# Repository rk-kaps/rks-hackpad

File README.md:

<h1 align="center">12-Key RP2040 Hackpad</h1>

<p align="center">
  A custom 12-key macropad built around the Seeed XIAO RP2040, featuring per-key RGB, an OLED display, and a 3D printed case.
</p>

<hr>

<h2>Motivation</h2>
<ul>

This Hackpad began as a simple volume controller. It evolved into a fully-featured macropad focused on:

- Speeding up workflows
- Reducing repetitive actions
- Providing intuitive visual feedback
- Maximizing functionality within hardware constraints

</ul>

<h2>Project Highlights</h2>
<ul>

- Dual-core RP2040 at up to 133MHz via the compact Seeed XIAO form factor
- Per-key RGB lighting using SK6812 MINI-E reverse-mount LEDs for clean underglow
- 0.91" OLED display for real-time visual feedback and animations
- Keyboard matrix protected by 1N4148 diodes for reliable n-key rollover
- Brass heatset inserts for durable, reusable screw connections in the 3D printed case
- Compact 12-key layout in a custom 3D printed two-piece shell

</ul>

<h2>Firmware Features</h2>
<ul>

- Acts as a USB numpad  
- LED pulses under each key when pressed  
- OLED plays a cat GIF on loop  

</ul>

<hr>

<h2>PCB & Schematic</h2>

<p align="center">
  
  <br><em>Schematic</em>
</p>

<p align="center">
  
  <br><em>PCB Layout (KiCad)</em>
</p>

<p align="center">
  
  <br><em>PCB 3D Render</em>
</p>

<hr>

<h2>Case Design</h2>

<p align="center">
  
  <br><em>Case CAD</em>
</p>

<hr>

<h2>Bill of Materials</h2>

> A full BOM with pricing and purchase links is available as a separate file.

| Part | Quantity |
|------|----------|
| Seeed XIAO RP2040 | 1 |
| MX-Style Switches | 12 |
| Through-hole 1N4148 Diodes | 12 |
| SK6812 MINI-E LEDs | 12 |
| 0.91" OLED Display (SSD1306 I2C 128×32) | 1 |
| Blank DSA Keycaps | 12 |
| M3×16 mm Cap Head Screws | 4 |
| M3×5 mm Brass Heatset Inserts | 4 |
| 3D Printed Case Top | 1 |
| 3D Printed Case Bottom | 1 |

<hr>

<h2>Firmware</h2>

Firmware is located in the `Deploy` folder. Flash directly to the RP2040 via USB drag-and-drop.

<hr>

<h2>Acknowledgements</h2>
<ul>

- Good people of Hack Club  

</ul>

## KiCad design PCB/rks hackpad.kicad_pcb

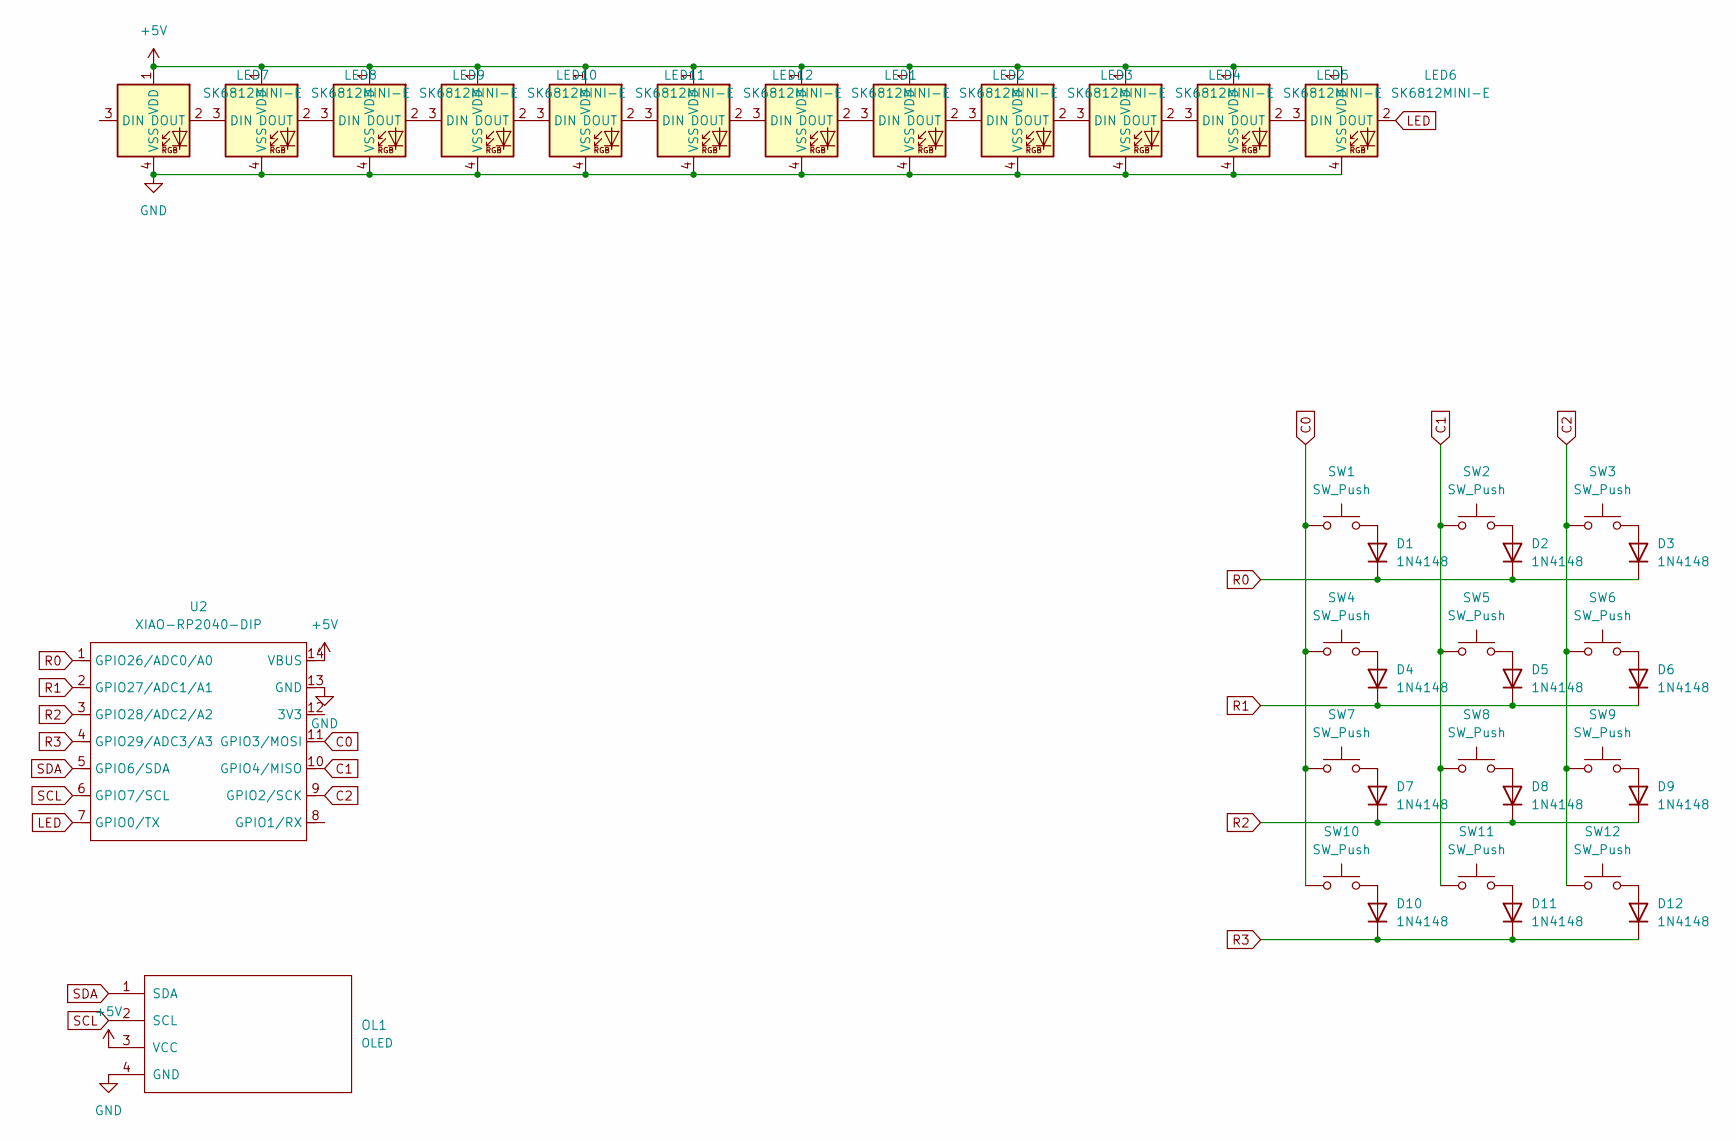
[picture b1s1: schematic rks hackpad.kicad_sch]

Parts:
D1, D2, D3, D4, D5, D6, D7, D8, D9, D10, D11, D12: 1N4148; D_DO-35_SOD27_P7.62mm_Horizontal
LED1, LED2, LED3, LED4, LED5, LED6, LED7, LED8, LED9, LED10, LED11, LED12: SK6812MINI-E; LED_6028R
OL1: OLED; Adafruit_SSD1306
SW1, SW2, SW3, SW4, SW5, SW6, SW7, SW8, SW9, SW10, SW11, SW12: SW_Push; SW_Cherry_MX_1.00u_PCB
U2: XIAO-RP2040-DIP

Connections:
+5V: LED1.1 (VDD), LED2.1 (VDD), LED3.1 (VDD), LED4.1 (VDD), LED5.1 (VDD), LED6.1 (VDD), LED7.1 (VDD), LED8.1 (VDD), LED9.1 (VDD), LED10.1 (VDD), LED11.1 (VDD), LED12.1 (VDD), OL1.3 (VCC), U2.14 (VBUS)
C0: SW1.1, SW4.1, SW7.1, SW10.1, U2.11 (GPIO3/MOSI)
C1: SW2.1, SW5.1, SW8.1, SW11.1, U2.10 (GPIO4/MISO)
C2: SW3.1, SW6.1, SW9.1, SW12.1, U2.9 (GPIO2/SCK)
GND: LED1.4 (VSS), LED2.4 (VSS), LED3.4 (VSS), LED4.4 (VSS), LED5.4 (VSS), LED6.4 (VSS), LED7.4 (VSS), LED8.4 (VSS), LED9.4 (VSS), LED10.4 (VSS), LED11.4 (VSS), LED12.4 (VSS), OL1.4 (GND), U2.13 (GND)
LED: LED6.2 (DOUT), U2.7 (GPIO0/TX)
unnamed: D1.2 (A), SW1.2
unnamed: D2.2 (A), SW2.2
unnamed: D3.2 (A), SW3.2
unnamed: D4.2 (A), SW4.2
unnamed: D5.2 (A), SW5.2
unnamed: D6.2 (A), SW6.2
unnamed: D7.2 (A), SW7.2
unnamed: D8.2 (A), SW8.2
unnamed: D9.2 (A), SW9.2
unnamed: D10.2 (A), SW10.2
unnamed: D11.2 (A), SW11.2
unnamed: D12.2 (A), SW12.2
unnamed: LED1.3 (DIN), LED12.2 (DOUT)
unnamed: LED1.2 (DOUT), LED2.3 (DIN)
unnamed: LED2.2 (DOUT), LED3.3 (DIN)
unnamed: LED3.2 (DOUT), LED4.3 (DIN)
unnamed: LED4.2 (DOUT), LED5.3 (DIN)
unnamed: LED5.2 (DOUT), LED6.3 (DIN)
unnamed: LED7.2 (DOUT), LED8.3 (DIN)
unnamed: LED8.2 (DOUT), LED9.3 (DIN)
unnamed: LED9.2 (DOUT), LED10.3 (DIN)
unnamed: LED10.2 (DOUT), LED11.3 (DIN)
unnamed: LED11.2 (DOUT), LED12.3 (DIN)
R0: D1.1 (K), D2.1 (K), D3.1 (K), U2.1 (GPIO26/ADC0/A0)
R1: D4.1 (K), D5.1 (K), D6.1 (K), U2.2 (GPIO27/ADC1/A1)
R2: D7.1 (K), D8.1 (K), D9.1 (K), U2.3 (GPIO28/ADC2/A2)
R3: D10.1 (K), D11.1 (K), D12.1 (K), U2.4 (GPIO29/ADC3/A3)
SCL: OL1.2 (SCL), U2.6 (GPIO7/SCL)
SDA: OL1.1 (SDA), U2.5 (GPIO6/SDA)

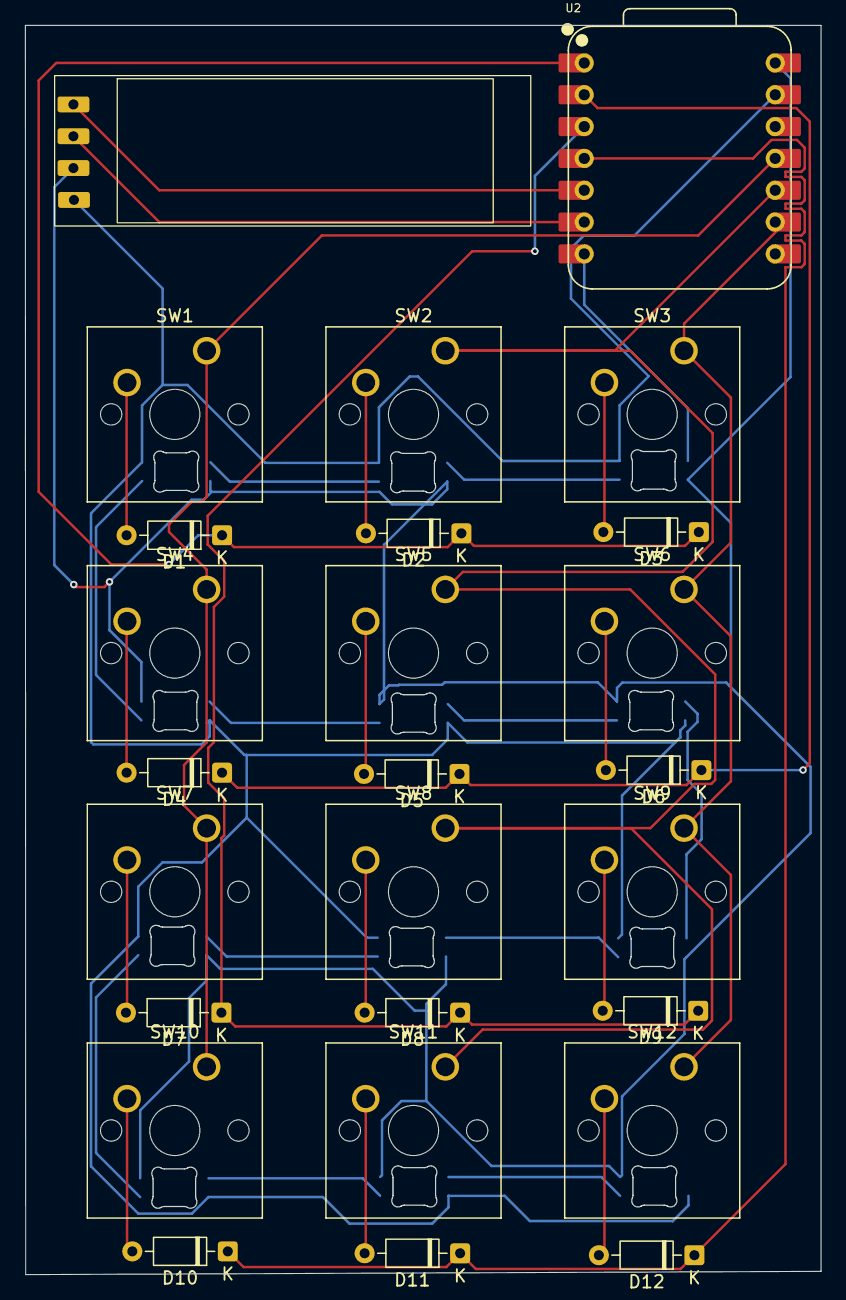
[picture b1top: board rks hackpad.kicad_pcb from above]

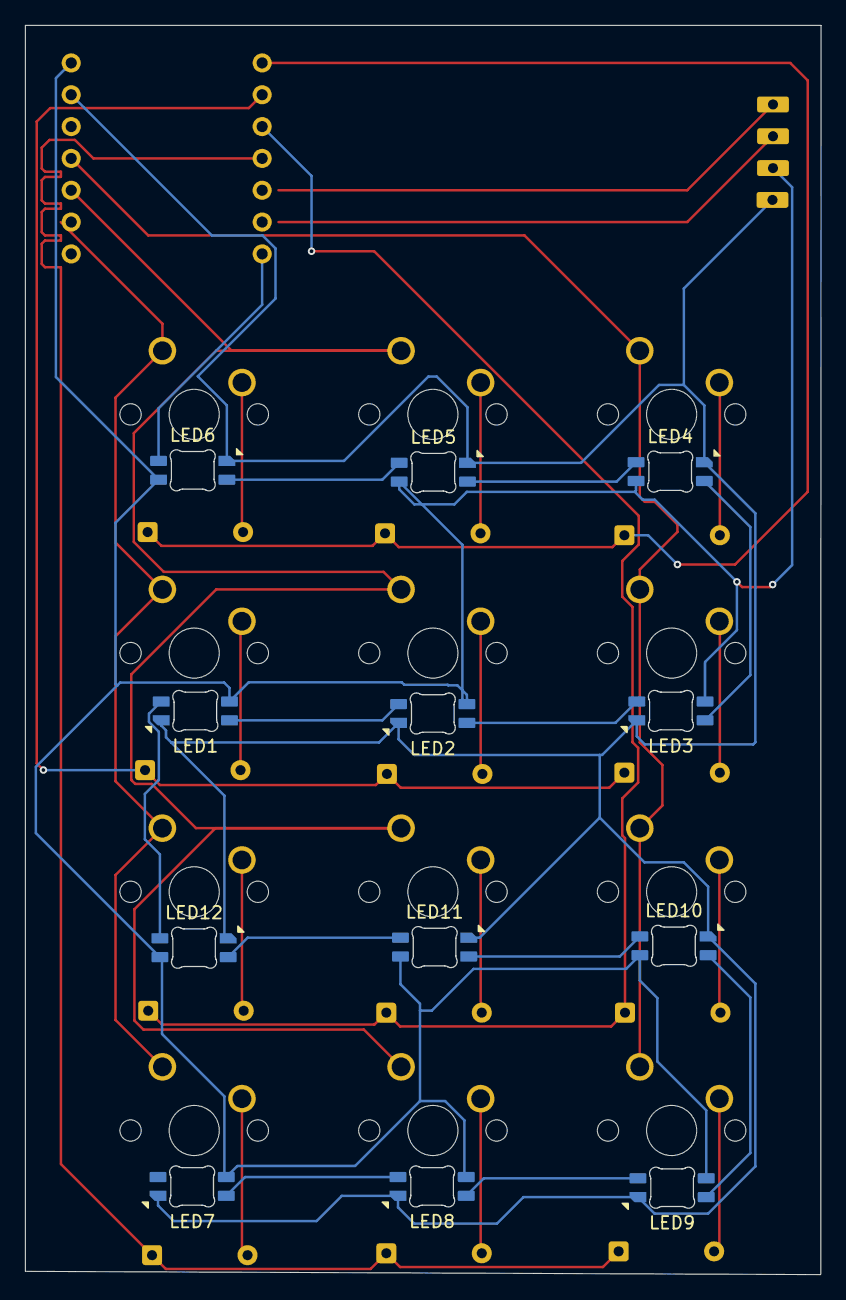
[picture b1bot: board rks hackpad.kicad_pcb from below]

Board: 2 copper layers, 63.5 x 99.7 mm, 38 parts (12 on the bottom side), 35 nets.

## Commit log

2026-04-04 Remove GIF to bitmap conversion instructions
    Removed instructions for converting GIFs to bitmaps.
2026-04-04 Update README.md
    Added a note about file organization in the README.
2026-04-04 Update README_hackpad (1).md
    Removed 'KMK Firmware Community' from acknowledgements.
2026-04-11 Enhance README with project details and features
    Expanded the README to provide detailed information about the 12-Key RP2040 Hackpad, including motivation, project highlights, firmware features, PCB & schematic, case design, bill of materials, and 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
2026-04-11 Update image source path in README
2026-04-11 Fix image source URL in README_hackpad
